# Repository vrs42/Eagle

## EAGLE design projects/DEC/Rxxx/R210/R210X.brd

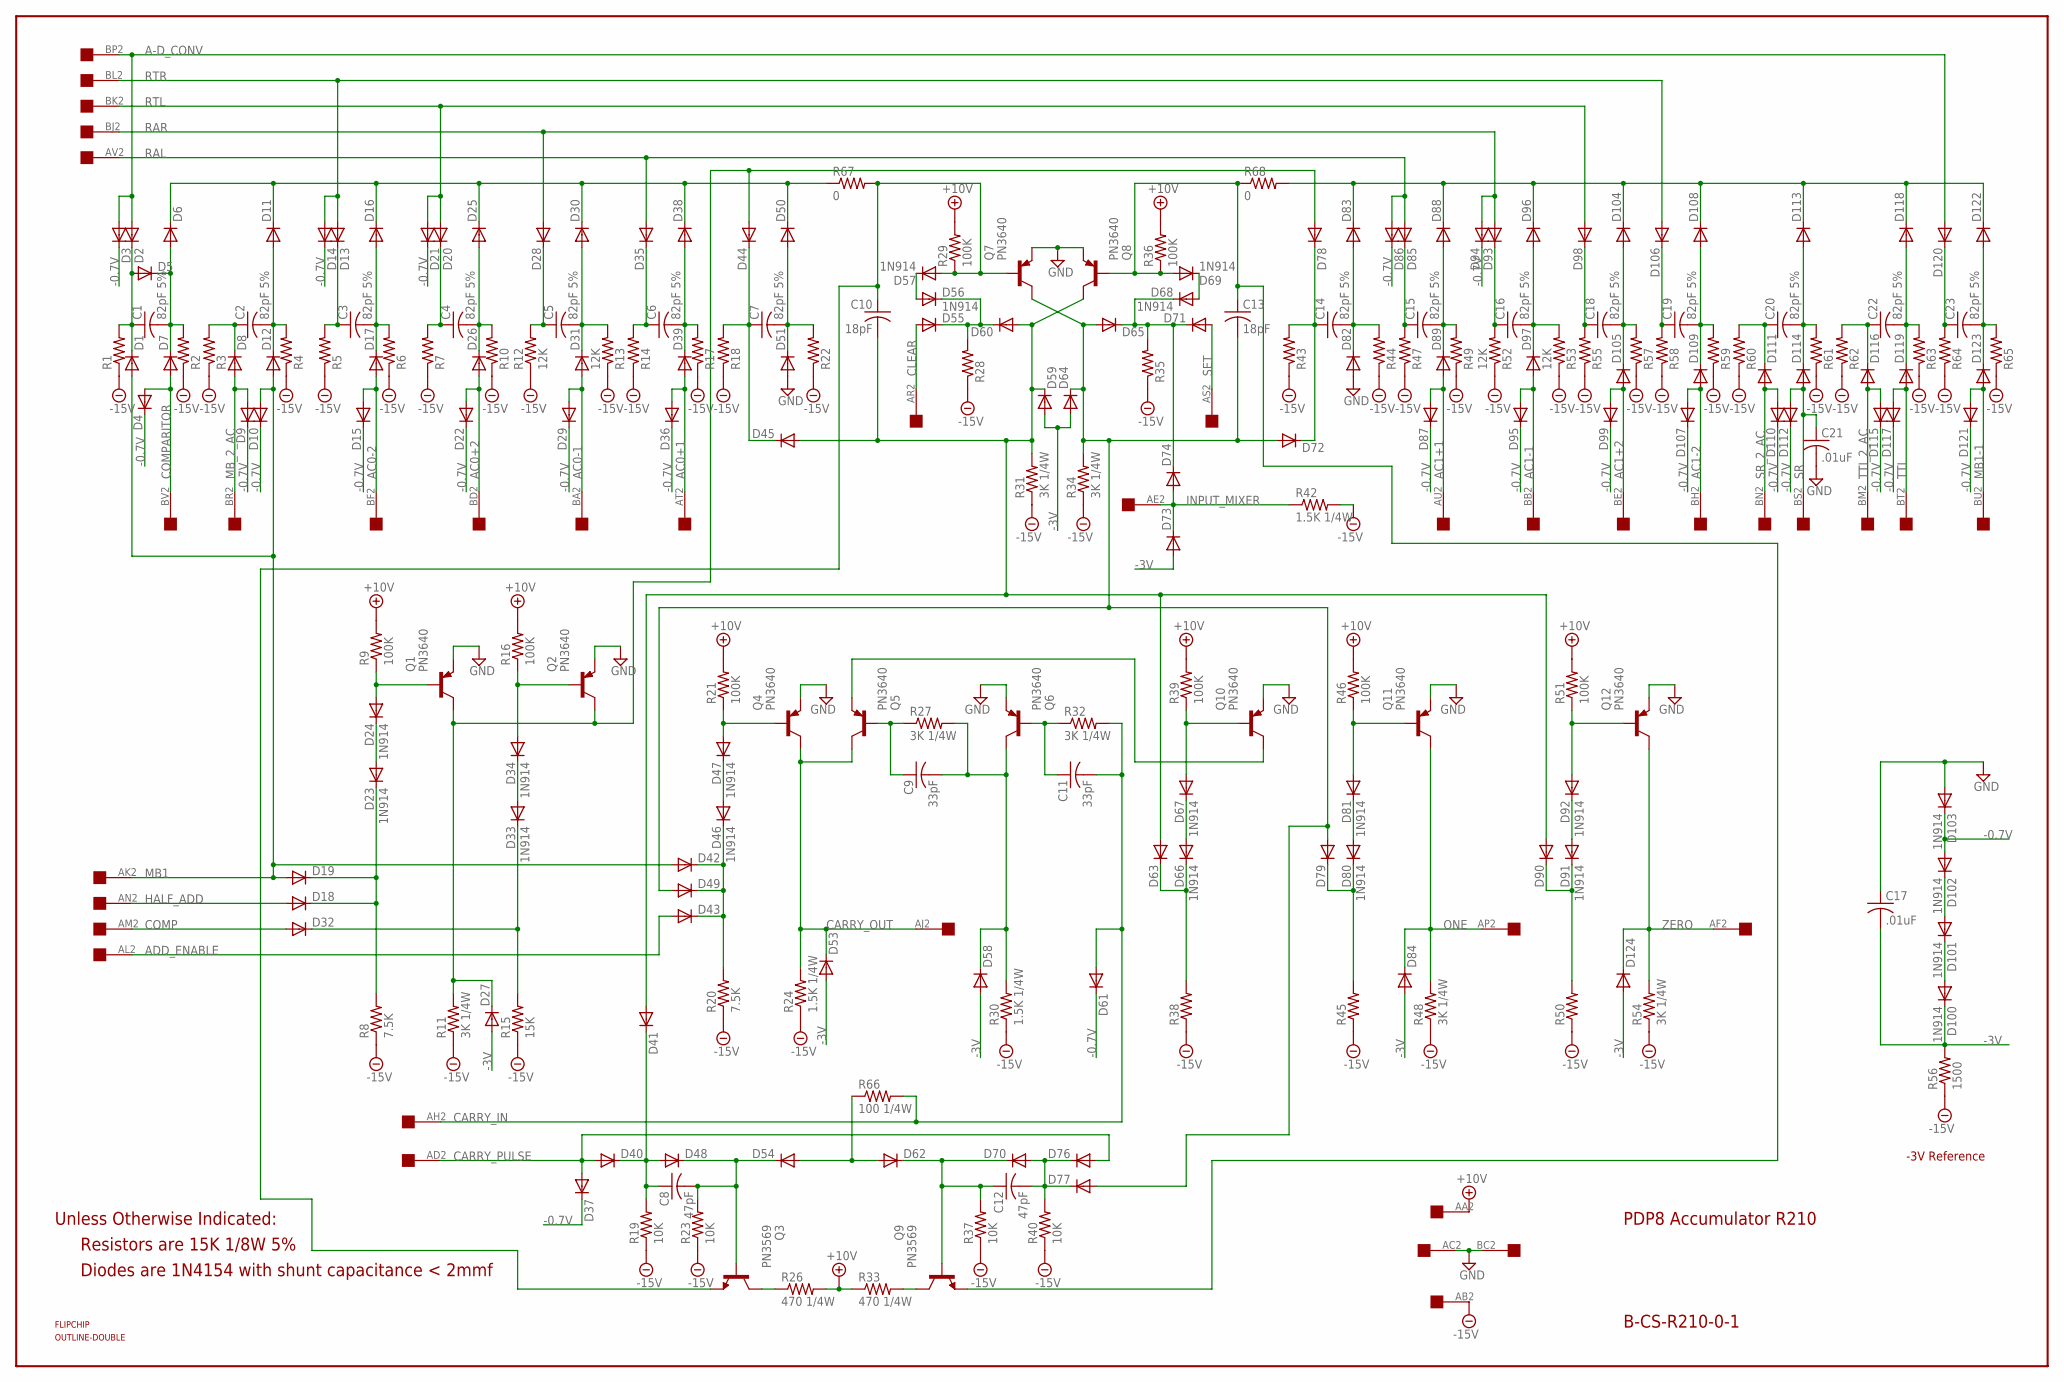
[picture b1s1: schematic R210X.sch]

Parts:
C1, C2, C3, C4, C5, C6, C7, C14, C15, C16, C18, C19, C20, C22, C23: 82pF 5%; C075-032X103
C8, C12: 47pF; C075-032X103
C9, C11: 33pF; C075-032X103
C10, C13: 18pF; C075-032X103
C17, C21: .01uF; C050-025X075
D1, D2, D3, D4, D5, D6, D7, D8, D9, D10, D11, D12, D13, D14, D15, D16, D17, D18, D19, D20, D21, D22, D25, D26, D27, D28, D29, D30, D31, D32, D35, D36, D37, D38, D39, D40, D41, D42, D43, D44, D45, D48, D49, D50, D51, D53, D54, D55, D58, D59, D60, D61, D62, D63, D64, D65, D70, D71, D72, D73, D74, D76, D77, D78, D79, D82, D83, D84, D85, D86, D87, D88, D89, D90, D93, D94, D95, D96, D97, D98, D99, D104, D105, D106, D107, D108, D109, D110, D111, D112, D113, D114, D115, D116, D117, D118, D119, D120, D121, D122, D123, D124: 1N4148DO35-10; DO35-10
D23, D24, D33, D34, D46, D47, D56, D57, D66, D67, D68, D69, D80, D81, D91, D92, D100, D101, D102, D103: 1N914; DO35-10
Q1, Q2, Q4, Q5, Q6, Q7, Q8, Q10, Q11, Q12: PN3640; TO39
Q3, Q9: PN3569; TO5
R1, R2, R3, R4, R5, R6, R7, R10, R14, R17, R18, R22, R28, R35, R38, R43, R44, R45, R47, R49, R50, R55, R57, R58, R59, R60, R61, R62, R63, R64, R65: R-US_0207/10; 0207/10
R8, R20: 7.5K; 0207/10
R9, R16, R21, R29, R36, R39, R46, R51: 100K; 0207/10
R11, R27, R31, R32, R34, R48, R54: 3K 1/4W; 0207/10
R12, R13, R52, R53: 12K; 0207/10
R15: 15K; 0207/10
R19, R23, R37, R40: 10K; 0207/10
R24, R30, R42: 1.5K 1/4W; 0207/10
R26, R33: 470 1/4W; 0207/10
R56: 1500; 0207/10
R66: 100 1/4W; 0207/10
R67, R68: 0; 0207/10
U$1: DOUBLE; EDGE-CON4
U$2: FLIPCHIP
U$3: OUTLINE-DOUBLE; DOUBLE

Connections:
+10V: R9.2, R16.2, R21.2, R26.2, R29.2, R33.1, R36.2, R39.2, R46.2, R51.2, U$1.AA2
-0.7V: D3.C, D4.C, D9.C, D10.C, D14.C, D15.C, D21.C, D22.C, D29.C, D36.C, D37.C, D61.C, D86.C, D87.C, D94.C, D95.C, D99.C, D102.A, D103.C, D107.C, D110.C, D112.C, D115.C, D117.C, D121.C
-3V: C17.2, D27.A, D53.A, D58.A, D59.A, D64.A, D73.A, D84.A, D100.C, D124.A, R56.2
-15V: R1.1, R2.1, R3.1, R4.1, R5.1, R6.1, R7.1, R8.1, R10.1, R11.1, R12.1, R13.1, R14.1, R15.1, R17.1, R18.1, R19.1, R20.1, R22.1, R23.1, R24.1, R28.1, R30.1, R31.1, R34.1, R35.1, R37.1, R38.1, R40.1, R42.2, R43.1, R44.1, R45.1, R47.1, R48.1, R49.1, R50.1, R52.1, R53.1, R54.1, R55.1, R56.1, R57.1, R58.1, R59.1, R60.1, R61.1, R62.1, R63.1, R64.1, R65.1, U$1.AB2
A-D_CONV: D2.A, D3.A, D120.A, U$1.BP2
AC0+1: D36.A, D39.A, U$1.AT2
AC0+2: D22.A, D26.A, U$1.BD2
AC0-1: D29.A, D31.A, U$1.BA2
AC0-2: D15.A, D17.A, U$1.BF2
AC1+1: D87.A, D89.A, U$1.AU2
AC1+2: D99.A, D105.A, U$1.BE2
AC1-1: D95.A, D97.A, U$1.BB2
AC1-2: D107.A, D109.A, U$1.BH2
ADD_ENABLE: D43.A, U$1.AL2
CARRY_IN: C11.2, D61.A, R32.2, R66.2, U$1.AH2
CARRY_OUT: D53.C, Q4.3 (C), Q5.3 (C), R24.2, U$1.AJ2
CARRY_PULSE: D37.A, D40.A, D76.A, U$1.AD2
CLEAR: D55.A, U$1.AR2
COMP: D32.A, U$1.AM2
COMPARITOR: D4.A, D7.A, U$1.BV2
GND: C17.1, C21.2, D51.A, D82.A, D103.A, Q1.1 (E), Q2.1 (E), Q4.1 (E), Q6.1 (E), Q7.1 (E), Q8.1 (E), Q10.1 (E), Q11.1 (E), Q12.1 (E), U$1.AC2, U$1.BC2
HALF_ADD: D18.A, U$1.AN2
INPUT_MIXER: D73.C, D74.A, R42.1, U$1.AE2
MB1: D1.A, D10.A, D12.A, D19.A, D42.A, U$1.AK2
MB1-1: D121.A, D123.A, U$1.BU2
MB_2_AC: D8.A, D9.A, U$1.BR2
unnamed: D6.C, D11.C, D16.C, D25.C, D30.C, D38.C, D50.C, R67.1
unnamed: D27.C, D44.A, D78.A, Q1.3 (C), Q2.3 (C), R11.2
unnamed: C1.2, D5.C, D6.A, D7.C, R2.2
unnamed: C1.1, D1.C, D2.C, D5.A, R1.2
unnamed: D18.C, D19.C, D23.C, R8.2
unnamed: C2.1, D8.C, R3.2
unnamed: C2.2, D11.A, D12.C, R4.2
unnamed: C10.2, D41.A, D45.A, D59.C, D60.A, D63.A, D90.A, Q8.3 (C), R31.2
unnamed: C13.2, D49.A, D64.C, D65.A, D72.A, D77.A, D79.A, Q7.3 (C), R34.2
unnamed: D55.C, D56.C, D60.C, R28.2
unnamed: D56.A, D57.C
unnamed: C3.1, D13.C, R5.2
unnamed: D101.A, D102.C
unnamed: C3.2, D16.A, D17.C, R6.2
unnamed: C10.1, D57.A, Q3.1 (E), Q7.2 (B), R29.1, R67.2
unnamed: D100.A, D101.C
unnamed: D66.A, D67.C
unnamed: C4.1, D20.C, R7.2
unnamed: C4.2, D25.A, D26.C, R10.2
unnamed: C13.1, D69.A, Q8.2 (B), Q9.1 (E), R36.1, R68.1
unnamed: D68.A, D69.C
unnamed: C5.1, D28.C, R12.2
unnamed: C5.2, D30.A, D31.C, R13.2
unnamed: D65.C, D68.C, D71.C, D74.C, R35.2
unnamed: D83.C, D88.C, D96.C, D104.C, D108.C, D113.C, D118.C, D122.C, R68.2
unnamed: C6.1, D35.C, R14.2
unnamed: C6.2, D38.A, D39.C, R17.2
unnamed: C12.1, D62.C, D70.C, Q9.2 (B), R37.2
unnamed: C14.1, D72.C, D78.C, R43.2
unnamed: C7.1, D44.C, D45.C, R18.2
unnamed: C7.2, D50.A, D51.C, R22.2
unnamed: C14.2, D82.C, D83.A, R44.2
unnamed: C15.1, D85.C, R47.2
unnamed: C15.2, D88.A, D89.C, R49.2
unnamed: C16.1, D93.C, R52.2
unnamed: C16.2, D96.A, D97.C, R53.2
unnamed: C18.1, D98.C, R55.2
unnamed: C18.2, D104.A, D105.C, R57.2
unnamed: D24.A, Q1.2 (B), R9.1
unnamed: D23.A, D24.C
unnamed: C19.1, D106.C, R58.2
unnamed: C19.2, D108.A, D109.C, R59.2
unnamed: D33.A, D34.C
unnamed: C20.1, D111.C, R60.2
unnamed: C20.2, D113.A, D114.C, R61.2
unnamed: C12.2, D70.A, D76.C, D77.C, R40.2
unnamed: D32.C, D33.C, R15.2
unnamed: C22.1, D116.C, R62.2
unnamed: C22.2, D118.A, D119.C, R63.2
unnamed: D34.A, Q2.2 (B), R16.1
unnamed: D47.A, Q4.2 (B), R21.1
unnamed: C23.1, D120.C, R64.2
unnamed: C23.2, D122.A, D123.C, R65.2
unnamed: D46.A, D47.C
unnamed: D42.C, D43.C, D46.C, D49.C, R20.2
unnamed: C9.1, Q5.2 (B), R27.1
unnamed: C9.2, D58.C, Q6.3 (C), R27.2, R30.2
unnamed: Q5.1 (E), Q10.3 (C)
unnamed: C11.1, Q6.2 (B), R32.1
unnamed: D54.A, D62.A, R66.1
unnamed: D67.A, Q10.2 (B), R39.1
unnamed: D63.C, D66.C, R38.2
unnamed: D81.A, Q11.2 (B), R46.1
unnamed: C8.1, D40.C, D41.C, D48.A, R19.2
unnamed: D80.A, D81.C
unnamed: D79.C, D80.C, R45.2
unnamed: D92.A, Q12.2 (B), R51.1
unnamed: D90.C, D91.C, R50.2
unnamed: D91.A, D92.C
unnamed: C8.2, D48.C, D54.C, Q3.2 (B), R23.2
unnamed: Q3.3 (C), R26.1
unnamed: Q9.3 (C), R33.2
ONE: D84.C, Q11.3 (C), R48.2, U$1.AP2
RAL: D35.A, D85.A, D86.A, U$1.AV2
RAR: D28.A, D93.A, D94.A, U$1.BJ2
RTL: D20.A, D21.A, D98.A, U$1.BK2
RTR: D13.A, D14.A, D106.A, U$1.BL2
SET: D71.A, U$1.AS2
SR: C21.1, D112.A, D114.A, U$1.BS2
SR_2_AC: D110.A, D111.A, U$1.BN2
TTI: D117.A, D119.A, U$1.BT2
TTI_2_AC: D115.A, D116.A, U$1.BM2
ZERO: D124.C, Q12.3 (C), R54.2, U$1.AF2

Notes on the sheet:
PDP8 Accumulator R210
B-CS-R210-0-1
-3V Reference
Resistors are 15K 1/8W 5%
Diodes are 1N4154 with shunt capacitance < 2mmf
Unless Otherwise Indicated:

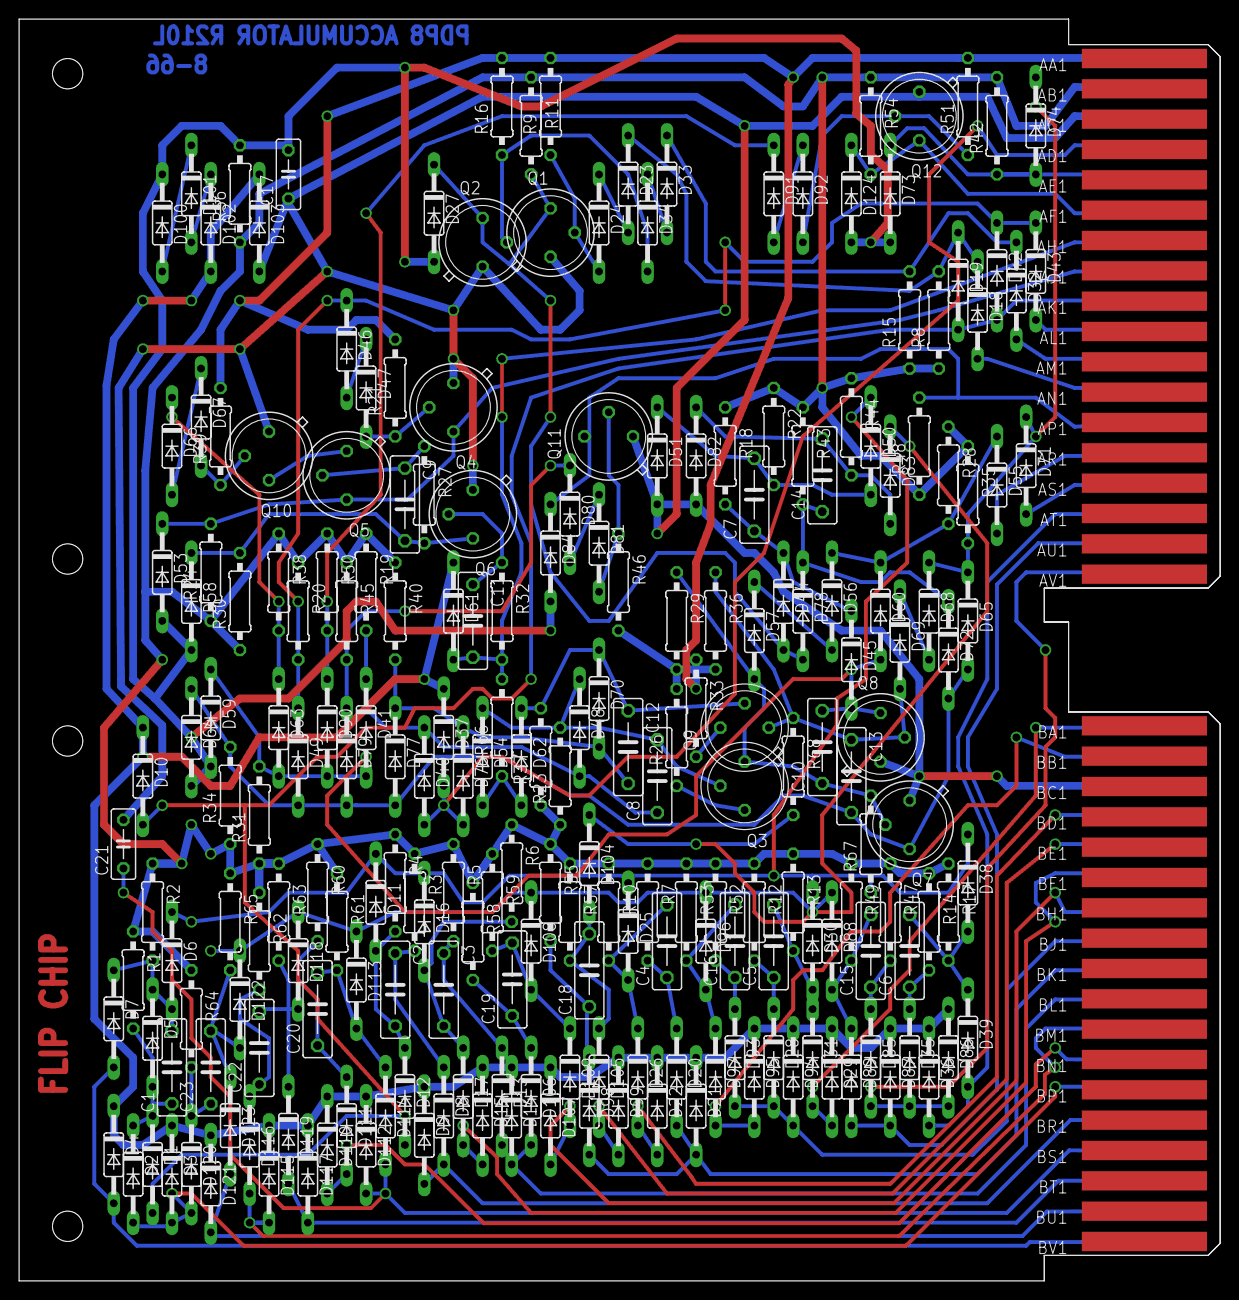
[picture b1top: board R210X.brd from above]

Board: 2 copper layers, 125.7 x 132.1 mm, 226 parts (0 on the bottom side), 109 nets.

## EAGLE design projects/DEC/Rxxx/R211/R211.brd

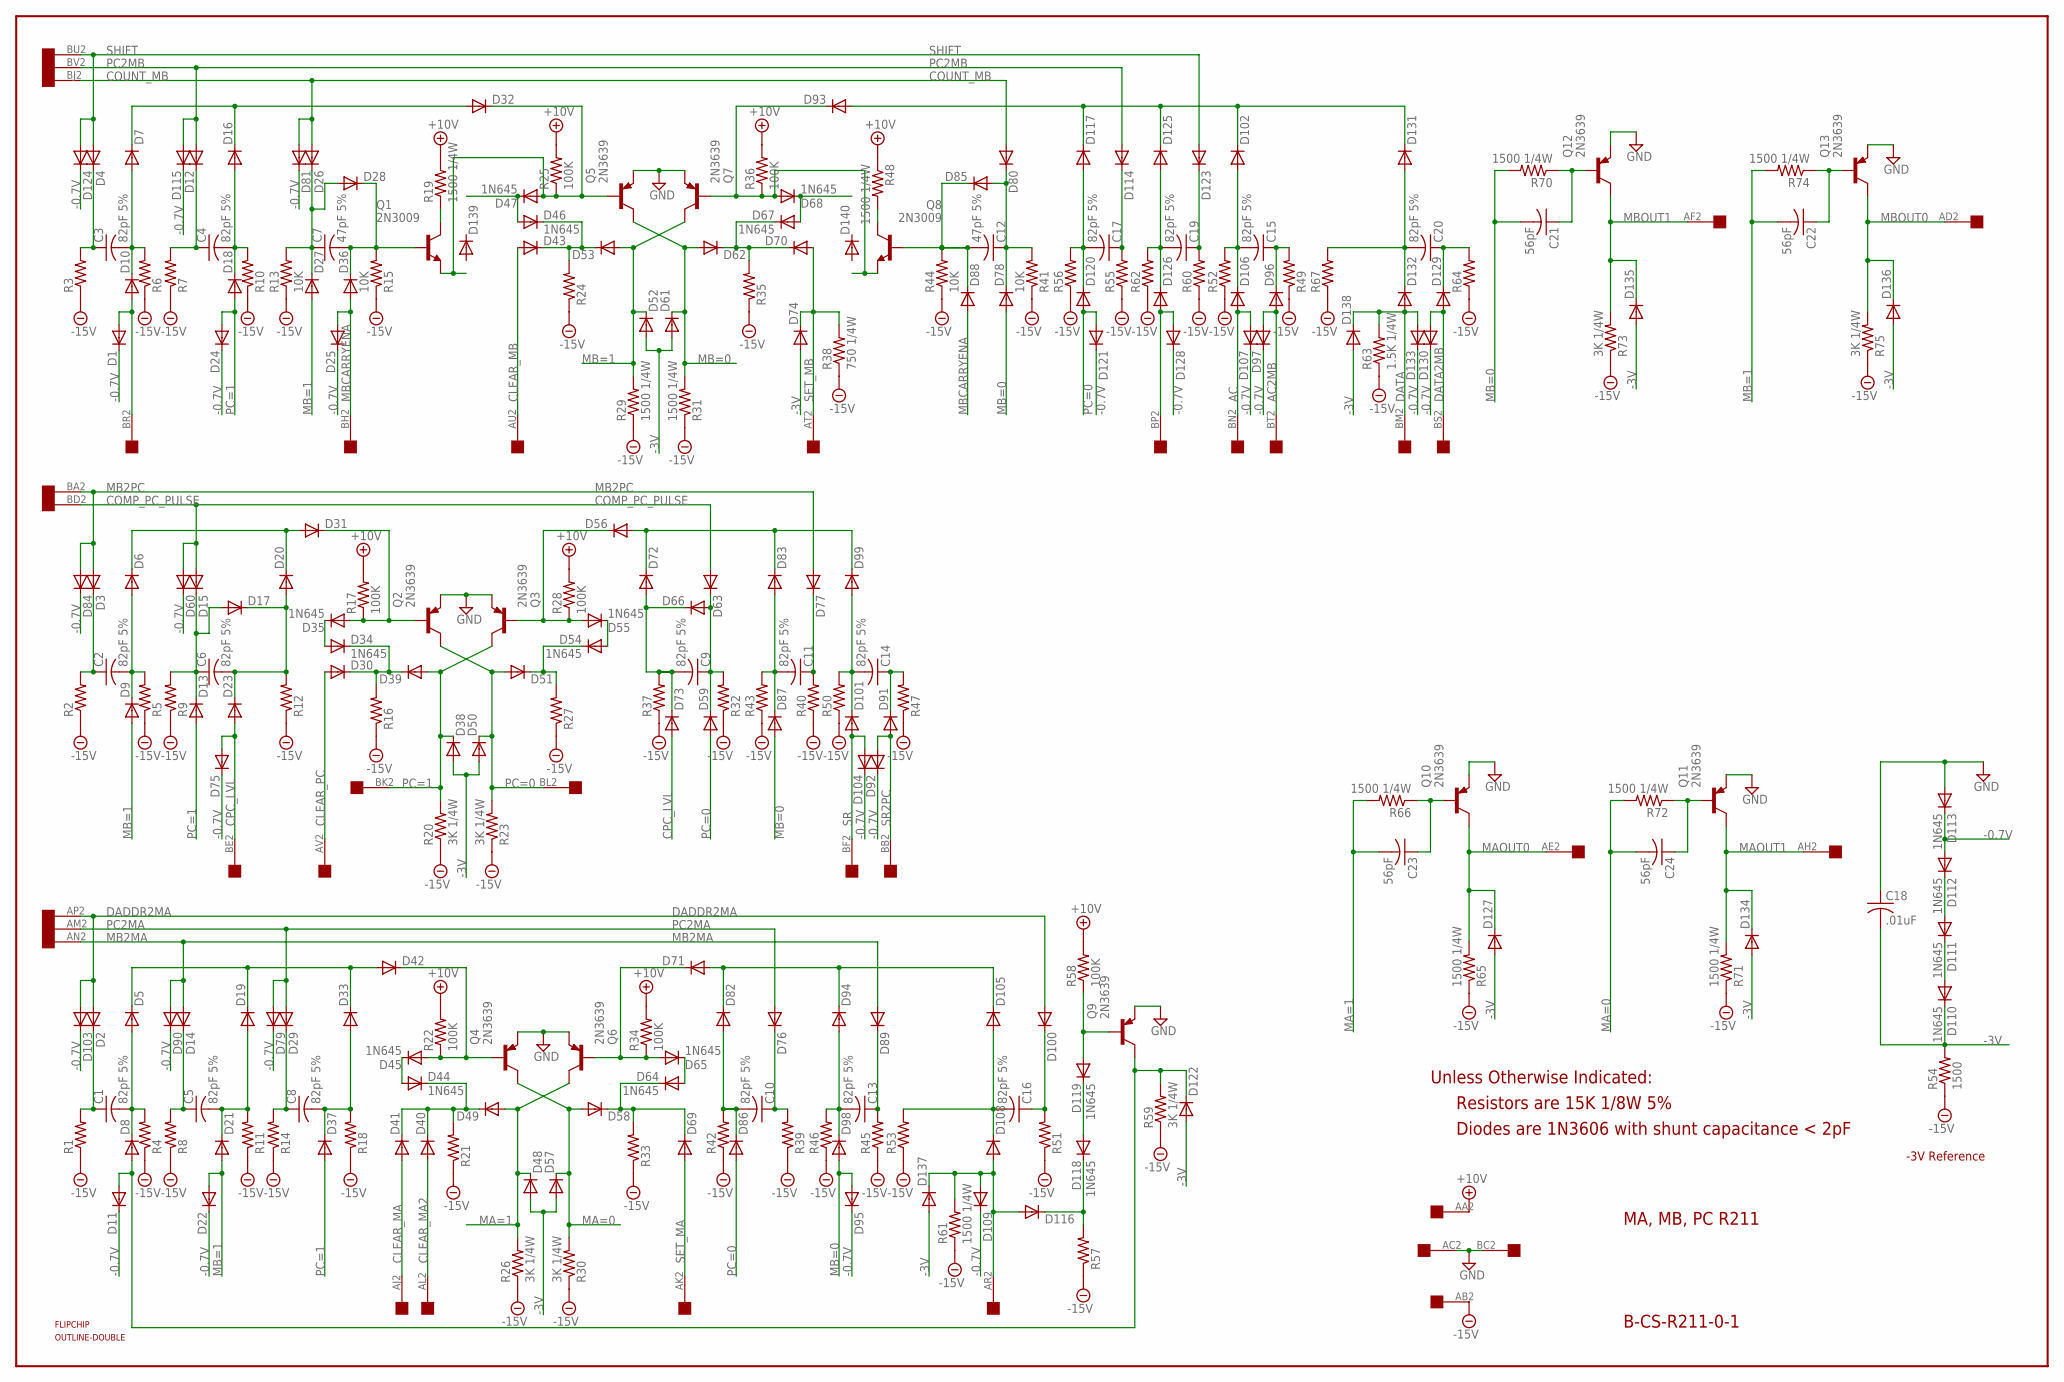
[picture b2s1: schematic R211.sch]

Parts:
C1, C2, C3, C4, C5, C6, C8, C9, C10, C11, C13, C14, C15, C16, C17, C19, C20: 82pF 5%; C050-025X075
C7, C12: 47pF 5%; C050-025X075
C18: .01uF; C050-025X075
C21, C22, C23, C24: 56pF; C050-025X075
D1, D2, D3, D4, D5, D6, D7, D8, D9, D10, D11, D12, D13, D14, D15, D16, D17, D18, D19, D20, D21, D22, D23, D24, D25, D26, D27, D28, D29, D30, D31, D32, D33, D36, D37, D38, D39, D40, D41, D42, D43, D48, D49, D50, D51, D52, D53, D56, D57, D58, D59, D60, D61, D62, D63, D66, D69, D70, D71, D72, D73, D74, D75, D76, D77, D78, D79, D80, D81, D82, D83, D84, D85, D86, D87, D88, D89, D90, D91, D92, D93, D94, D95, D96, D97, D98, D99, D100, D101, D102, D103, D104, D105, D106, D107, D108, D109, D114, D115, D116, D117, D120, D121, D122, D123, D124, D125, D126, D127, D128, D129, D130, D131, D132, D133, D134, D135, D136, D137, D138, D139, D140: 1N4148DO35-10; DO35-10
D34, D35, D44, D45, D46, D47, D54, D55, D64, D65, D67, D68, D110, D111, D112, D113, D118, D119: 1N645; DO35-10
Q1, Q8: 2N3009; TO5
Q2, Q3, Q4, Q5, Q6, Q7, Q9, Q10, Q11, Q12, Q13: 2N3639; TO39
R1, R2, R3, R4, R5, R6, R7, R8, R9, R10, R11, R12, R14, R16, R18, R21, R24, R27, R32, R33, R35, R37, R39, R40, R42, R43, R45, R46, R47, R49, R50, R51, R52, R53, R55, R56, R57, R60, R62, R64, R67: R-US_0207/10; 0207/10
R13, R15, R41, R44: 10K; 0207/10
R17, R22, R25, R28, R34, R36, R58: 100K; 0207/10
R19, R29, R31, R48, R61, R65, R66, R70, R71, R72, R74: 1500 1/4W; 0207/10
R20, R23, R26, R30, R59, R73, R75: 3K 1/4W; 0207/10
R38: 750 1/4W; 0207/10
R54: 1500; 0207/10
R63: 1.5K 1/4W; 0207/10
U$1: DOUBLE; EDGE-CON4
U$2: FLIPCHIP
U$3: OUTLINE-DOUBLE; DOUBLE

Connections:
+10V: R17.2, R19.2, R22.2, R25.2, R28.2, R34.2, R36.2, R48.1, R58.2, U$1.AA2
-0.7V: D1.C, D11.C, D22.C, D24.C, D25.C, D60.C, D75.C, D79.C, D81.C, D84.C, D90.C, D92.C, D95.C, D97.C, D103.C, D104.C, D107.C, D109.C, D112.A, D113.C, D115.C, D121.C, D124.C, D128.C, D130.C, D133.C
-3V: C18.2, D38.A, D48.A, D50.A, D52.A, D57.A, D61.A, D74.A, D110.C, D122.A, D127.A, D134.A, D135.A, D136.A, D137.A, D138.A, R54.2
-15V: R1.1, R2.1, R3.1, R4.1, R5.1, R6.1, R7.1, R8.1, R9.1, R10.1, R11.1, R12.1, R13.1, R14.1, R15.1, R16.1, R18.1, R20.1, R21.1, R23.1, R24.1, R26.1, R27.1, R29.1, R30.1, R31.1, R32.1, R33.1, R35.1, R37.1, R38.1, R39.1, R40.1, R41.1, R42.1, R43.1, R44.1, R45.1, R46.1, R47.1, R49.1, R50.1, R51.1, R52.1, R53.1, R54.1, R55.1, R56.1, R57.1, R59.1, R60.1, R61.1, R62.1, R63.1, R64.1, R65.1, R67.1, R71.1, R73.1, R75.1, U$1.AB2
AC: D106.A, D107.A, U$1.BN2
AC2MB: D96.A, D97.A, U$1.BT2
CLEAR_MA: D41.A, U$1.AJ2
CLEAR_MA2: D40.A, U$1.AL2
CLEAR_MB: D43.A, U$1.AU2
CLEAR_PC: D30.A, U$1.AV2
COMP_PC_PULSE: D15.A, D60.A, D63.A, U$1.BD2
COUNT_MB: D26.A, D80.A, D81.A, U$1.BJ2
CPC_LVL: D23.A, D73.A, D75.A, U$1.BE2
DADDR2MA: D2.A, D100.A, D103.A, U$1.AP2
DATA: D132.A, D133.A, D138.C, R63.2, U$1.BM2
DATA2MB: D129.A, D130.A, U$1.BS2
GND: C18.1, D113.A, Q2.1 (E), Q3.1 (E), Q4.1 (E), Q5.1 (E), Q6.1 (E), Q7.1 (E), Q9.1 (E), Q10.1 (E), Q11.1 (E), Q12.1 (E), Q13.1 (E), U$1.AC2, U$1.BC2
MA=0: C24.2, D57.C, D58.A, Q4.3 (C), R30.2, R72.2
MA=1: C23.2, D48.C, D49.A, Q6.3 (C), R26.2, R66.2
MAOUT0: D127.C, Q10.3 (C), R65.2, U$1.AE2
MAOUT1: D134.C, Q11.3 (C), R71.2, U$1.AH2
MB2MA: D14.A, D89.A, D90.A, U$1.AN2
MB2PC: D3.A, D77.A, D84.A, U$1.BA2
MB=0: C21.2, D61.C, D62.A, D78.A, D87.A, D95.A, D98.A, Q5.3 (C), R31.2, R70.2
MB=1: C22.2, D9.A, D21.A, D22.A, D27.A, D52.C, D53.A, Q7.3 (C), R29.2, R74.2
MBCARRYENA: D25.A, D36.A, D88.A, U$1.BH2
MBOUT0: D136.C, Q13.3 (C), R75.2, U$1.AD2
MBOUT1: D135.C, Q12.3 (C), R73.2, U$1.AF2
unnamed: D7.C, D16.C, D32.A
unnamed: C2.2, D6.A, D9.C, R5.2
unnamed: C3.2, D7.A, D10.C, R6.2
unnamed: C3.1, D4.C, R3.2
unnamed: C2.1, D3.C, R2.2
unnamed: C4.1, D12.C, R7.2
unnamed: C4.2, D16.A, D18.C, R10.2
unnamed: Q1.3 (C), R19.1
unnamed: D46.A, D47.C
unnamed: D43.C, D46.C, D53.C, R24.2
unnamed: D32.C, D47.A, Q1.1 (E), Q5.2 (B), R25.1
unnamed: C7.1, D26.C, D27.C, D28.A, R13.2
unnamed: D111.A, D112.C
unnamed: C7.2, D28.C, D36.C, Q1.2 (B), R15.2
unnamed: D93.A, D102.C, D117.C, D125.C, D131.C
unnamed: D110.A, D111.C
unnamed: C1.2, D5.A, D8.C, R4.2
unnamed: D67.A, D68.C
unnamed: D62.C, D67.C, D70.C, R35.2
unnamed: C12.2, D85.C, D88.C, Q8.2 (B), R44.2
unnamed: D68.A, D93.C, Q7.2 (B), Q8.1 (E), R36.1
unnamed: C1.1, D2.C, R1.2
unnamed: D5.C, D19.C, D33.C, D42.A
unnamed: C13.2, D94.A, D98.C, R46.2
unnamed: D126.A, D128.A, U$1.BP2
unnamed: C5.1, D14.C, R8.2
unnamed: D6.C, D20.C, D31.A
unnamed: C6.1, D13.C, D15.C, D17.A, R9.2
unnamed: C6.2, D17.C, D20.A, D23.C, R12.2
unnamed: D30.C, D34.C, D39.C, R16.2
unnamed: D54.A, D55.C
unnamed: C9.1, D59.C, D63.C, D66.A, R32.2
unnamed: C11.1, D77.C, R40.2
unnamed: C11.2, D83.A, D87.C, R43.2
unnamed: C12.1, D78.C, D80.C, D85.A, R41.2
unnamed: C14.1, D91.C, R47.2
unnamed: C14.2, D99.A, D101.C, R50.2
unnamed: C5.2, D19.A, D21.C, R11.2
unnamed: C17.1, D114.C, R55.2
unnamed: C17.2, D117.A, D120.C, R56.2
unnamed: D1.A, D10.A, U$1.BR2
unnamed: D40.C, D41.C, D44.C, D49.C, R21.2
unnamed: C15.1, D96.C, R49.2
unnamed: C15.2, D102.A, D106.C, R52.2
unnamed: D64.A, D65.C
unnamed: C10.1, D76.C, R39.2
unnamed: C20.1, D129.C, R64.2
unnamed: C20.2, D131.A, D132.C, R67.2
unnamed: C13.1, D89.C, R45.2
unnamed: C19.1, D123.C, R60.2
unnamed: C19.2, D125.A, D126.C, R62.2
unnamed: C16.1, D100.C, R51.2
unnamed: C16.2, D105.A, D108.C, R53.2
unnamed: C22.1, Q13.2 (B), R74.1
unnamed: D108.A, D109.A, D116.A, D137.C, R61.2, U$1.AR2
unnamed: D44.A, D45.C
unnamed: C21.1, Q12.2 (B), R70.1
unnamed: D71.A, D82.C, D94.C, D105.C
unnamed: D58.C, D64.C, D69.C, R33.2
unnamed: D34.A, D35.C
unnamed: D56.A, D72.C, D83.C, D99.C
unnamed: D51.C, D54.C, R27.2
unnamed: C10.2, D82.A, D86.C, R42.2
unnamed: C9.2, D66.C, D72.A, D73.C, R37.2
unnamed: D42.C, D45.A, Q4.2 (B), R22.1
unnamed: D65.A, D71.C, Q6.2 (B), R34.1
unnamed: D31.C, D35.A, Q2.2 (B), R17.1
unnamed: D55.A, D56.C, Q3.2 (B), R28.1
unnamed: D8.A, D11.A, D122.C, Q9.3 (C), R59.2
unnamed: Q8.3 (C), R48.2
unnamed: C24.1, Q11.2 (B), R72.1
unnamed: C23.1, Q10.2 (B), R66.1
unnamed: C8.1, D29.C, R14.2
unnamed: C8.2, D33.A, D37.C, R18.2
unnamed: D116.C, D118.C, R57.2
unnamed: D118.A, D119.C
unnamed: D119.A, Q9.2 (B), R58.1
PC2MA: D29.A, D76.A, D79.A, U$1.AM2
PC2MB: D12.A, D114.A, D115.A, U$1.BV2
PC=0: D50.C, D51.A, D59.A, D86.A, D120.A, D121.A, Q2.3 (C), R23.2, U$1.BL2
PC=1: D13.A, D18.A, D24.A, D37.A, D38.C, D39.A, Q3.3 (C), R20.2, U$1.BK2
SET_MA: D69.A, U$1.AK2
SET_MB: D70.A, D74.C, R38.2, U$1.AT2
SHIFT: D4.A, D123.A, D124.A, U$1.BU2
SR: D101.A, D104.A, U$1.BF2
SR2PC: D91.A, D92.A, U$1.BB2

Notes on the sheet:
MA, MB, PC R211
B-CS-R211-0-1
-3V Reference
Resistors are 15K 1/8W 5%
Diodes are 1N3606 with shunt capacitance < 2pF
Unless Otherwise Indicated:

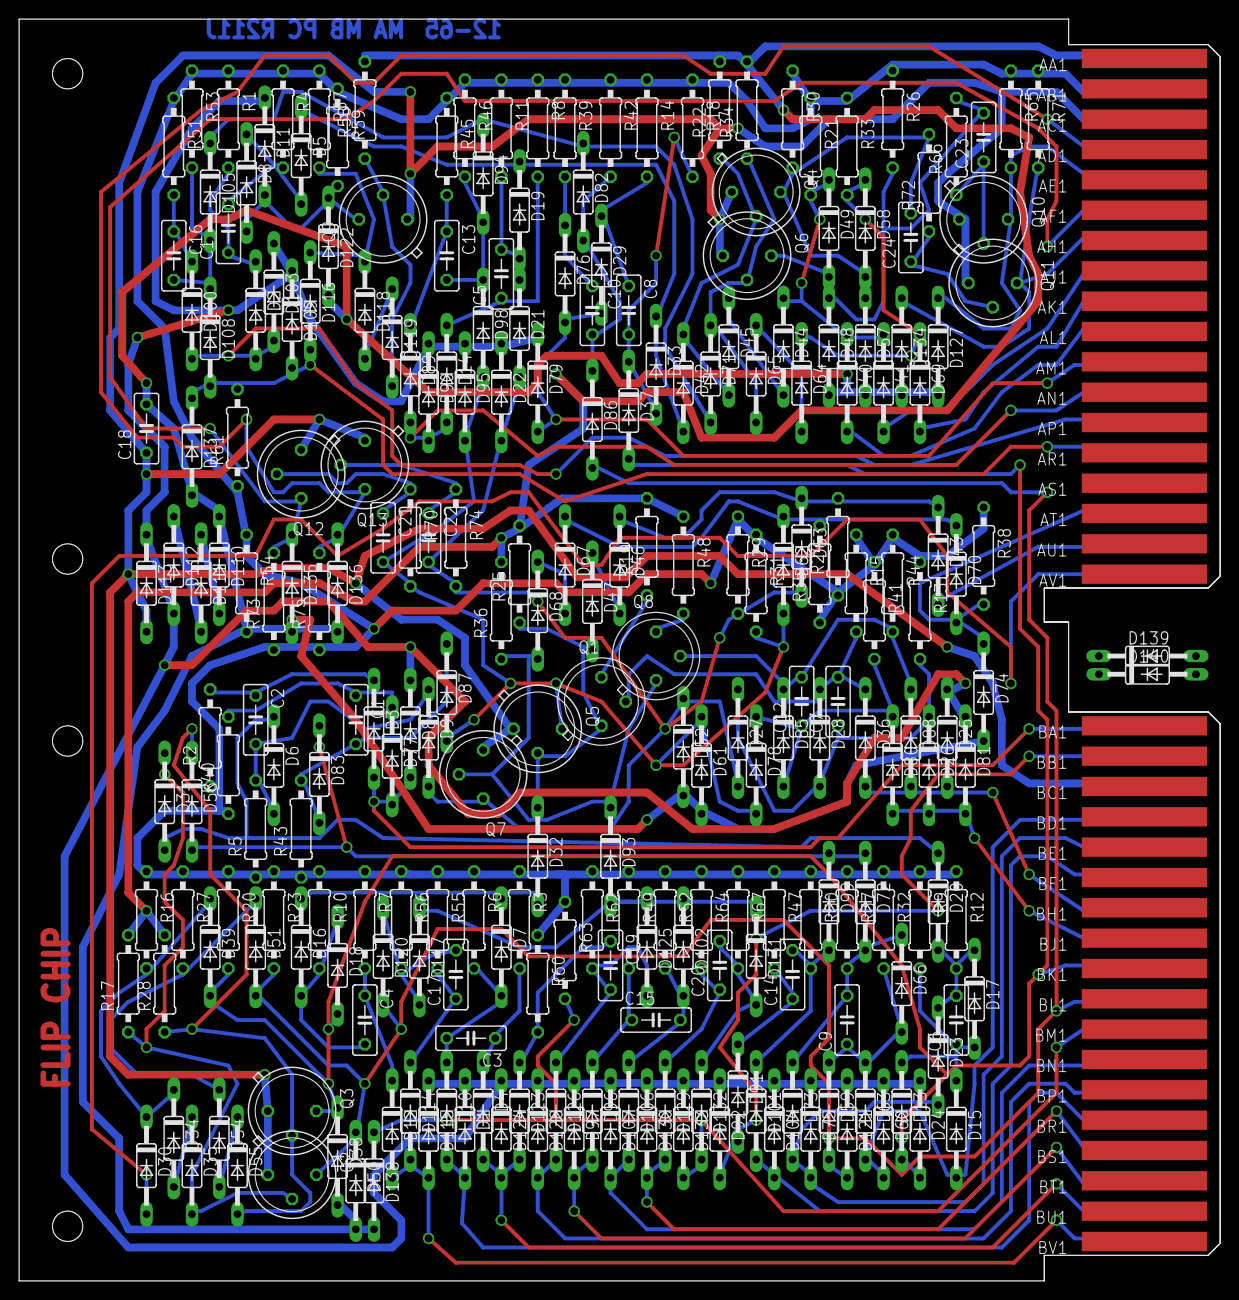
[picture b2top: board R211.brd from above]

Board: 2 copper layers, 125.7 x 132.1 mm, 253 parts (0 on the bottom side), 114 nets.

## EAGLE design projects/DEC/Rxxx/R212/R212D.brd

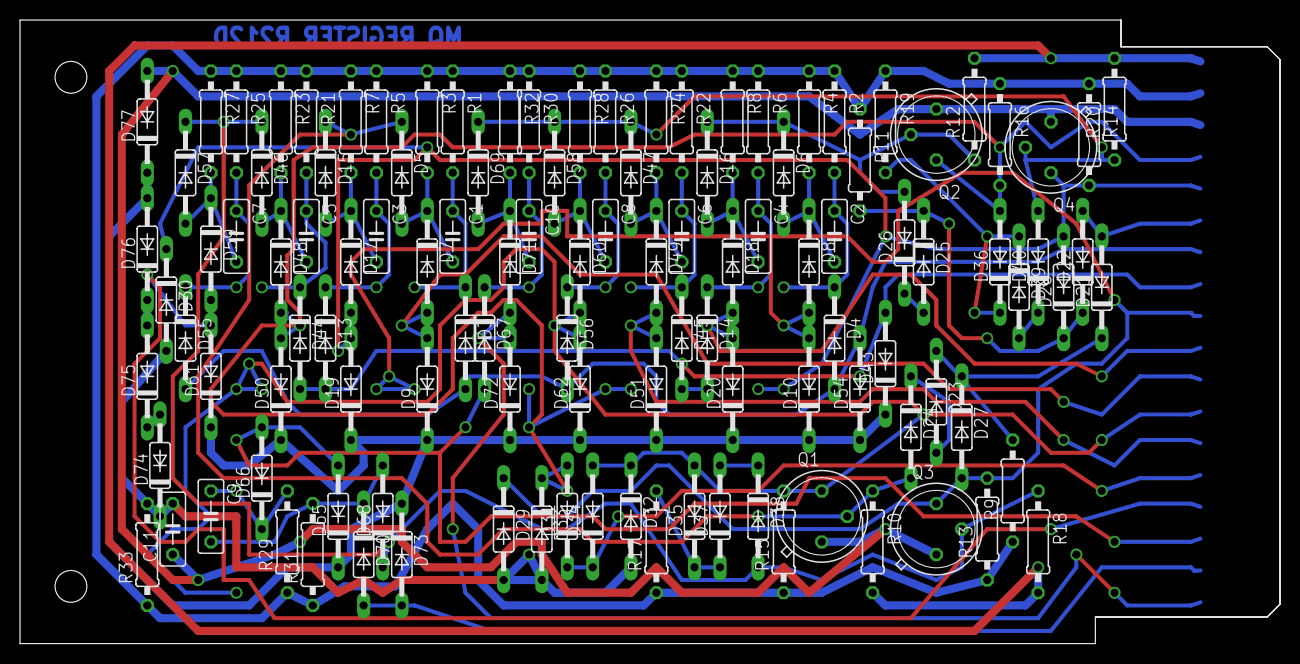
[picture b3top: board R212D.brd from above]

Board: 2 copper layers, 125.7 x 62.2 mm, 117 parts (0 on the bottom side), 54 nets.

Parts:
C1, C2, C3, C4, C5, C6, C7, C8, C9, C10: 82pF 5%; C050-025X075
C11: .01uf; C050-025X075
D3, D4, D5, D6, D7, D8, D9, D10, D13, D14, D15, D16, D17, D18, D19, D20, D21, D22, D27, D28, D29, D30, D31, D32, D33, D34, D35, D36, D43, D44, D45, D46, D47, D48, D49, D50, D51, D54, D55, D56, D57, D58, D59, D60, D61, D62, D65, D66, D67, D68, D69, D70, D71, D72, D73: 1N3606; DO35-10
D23, D24, D25, D26, D37, D38, D39, D40, D74, D75, D76, D77: 1N645; DO35-10
Q1, Q2, Q3, Q4: 2N3639; TO39
R1, R2, R3, R4, R5, R6, R7, R8, R21, R22, R23, R24, R25, R26, R27, R28, R29, R30, R31, R32: 12K; 0207/10
R9, R11, R17, R19: 15K; 0207/10
R10, R12, R18, R20: 100K; 0207/10
R13, R14, R15, R16: 3K; 0207/10
R33: 1500; 0207/10
U$1: OUTLINE-SINGLE; SINGLE
U$2: EDGE-1; EDGE-CON1

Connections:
+10V: R10.2, R12.2, R18.2, R20.2, U$2.A2
-0.7V: D9.C, D10.C, D19.C, D20.C, D43.C, D50.C, D51.C, D54.C, D61.C, D62.C, D65.C, D72.C, D73.C, D76.A, D77.C
-3V: C11.2, D29.A, D30.A, D32.A, D33.A, D74.C, R33.2
-15V: R1.1, R2.1, R3.1, R4.1, R5.1, R6.1, R7.1, R8.1, R9.1, R11.1, R13.1, R14.1, R15.1, R16.1, R17.1, R19.1, R21.1, R22.1, R23.1, R24.1, R25.1, R26.1, R27.1, R28.1, R29.1, R30.1, R31.1, R32.1, R33.1, U$2.B2
AC2MQ: D65.A, D66.A, D67.A, U$2.T2
GND: C11.1, D77.A, Q1.1, Q2.1, Q3.1, Q4.1, U$2.C2
MQA=0: D31.A, D33.C, D36.A, D48.A, D50.A, Q2.3, R16.2, U$2.D2
MQA=1: D17.A, D19.A, D28.A, D30.C, Q4.3, R14.2, U$2.E2
MQB=0: D32.C, D34.A, D35.A, D60.A, D62.A, Q1.3, R15.2, U$2.N2
MQB=1: D8.A, D10.A, D27.A, D29.C, Q3.3, R13.2, U$2.K2
unnamed: D6.C, D16.C, D26.A, Q2.2, R12.1
unnamed: C2.1, D4.C, R2.2
unnamed: C2.2, D6.A, D8.C, R4.2
unnamed: C10.1, D67.C, R30.2
unnamed: C4.1, D14.C, R6.2
unnamed: C4.2, D16.A, D18.C, R8.2
unnamed: D18.A, D20.A, U$2.L2
unnamed: D22.C, D25.C, D28.C, R11.2
unnamed: D25.A, D26.C
unnamed: C10.2, D69.A, D71.C, R32.2
unnamed: D71.A, D72.A, U$2.V2
unnamed: D40.A, D47.C, D58.C, D69.C, Q4.2, R20.1
unnamed: D75.A, D76.C
unnamed: D31.C, D34.C, U$2.R2
unnamed: C8.1, D56.C, R26.2
unnamed: D74.A, D75.C
unnamed: C8.2, D58.A, D60.C, R28.2
unnamed: D5.C, D15.C, D24.A, Q1.2, R10.1
unnamed: C6.1, D45.C, R22.2
unnamed: C6.2, D47.A, D49.C, R24.2
unnamed: D49.A, D51.A, U$2.P2
unnamed: D36.C, D39.C, R19.2
unnamed: D39.A, D40.C
unnamed: C3.1, D13.C, R5.2
unnamed: C3.2, D15.A, D17.C, R7.2
unnamed: C1.1, D3.C, R1.2
unnamed: C1.2, D5.A, D7.C, R3.2
unnamed: D7.A, D9.A, U$2.M2
unnamed: D21.C, D23.C, D27.C, R9.2
unnamed: D23.A, D24.C
unnamed: C5.1, D44.C, R21.2
unnamed: C5.2, D46.A, D48.C, R23.2
unnamed: C7.1, D55.C, R25.2
unnamed: C7.2, D57.A, D59.C, R27.2
unnamed: D59.A, D61.A, U$2.S2
unnamed: D35.C, D37.C, R17.2
unnamed: D37.A, D38.C
unnamed: D38.A, D46.C, D57.C, D68.C, Q3.2, R18.1
unnamed: C9.1, D66.C, R29.2
unnamed: C9.2, D68.A, D70.C, R31.2
unnamed: D70.A, D73.A, U$2.U2
SHIFT_LEFT: D3.A, D4.A, D54.A, D55.A, D56.A, U$2.H2
SHIFT_RIGHT: D13.A, D14.A, D43.A, D44.A, D45.A, U$2.J2
ZERO2MQ: D21.A, D22.A, U$2.F2
